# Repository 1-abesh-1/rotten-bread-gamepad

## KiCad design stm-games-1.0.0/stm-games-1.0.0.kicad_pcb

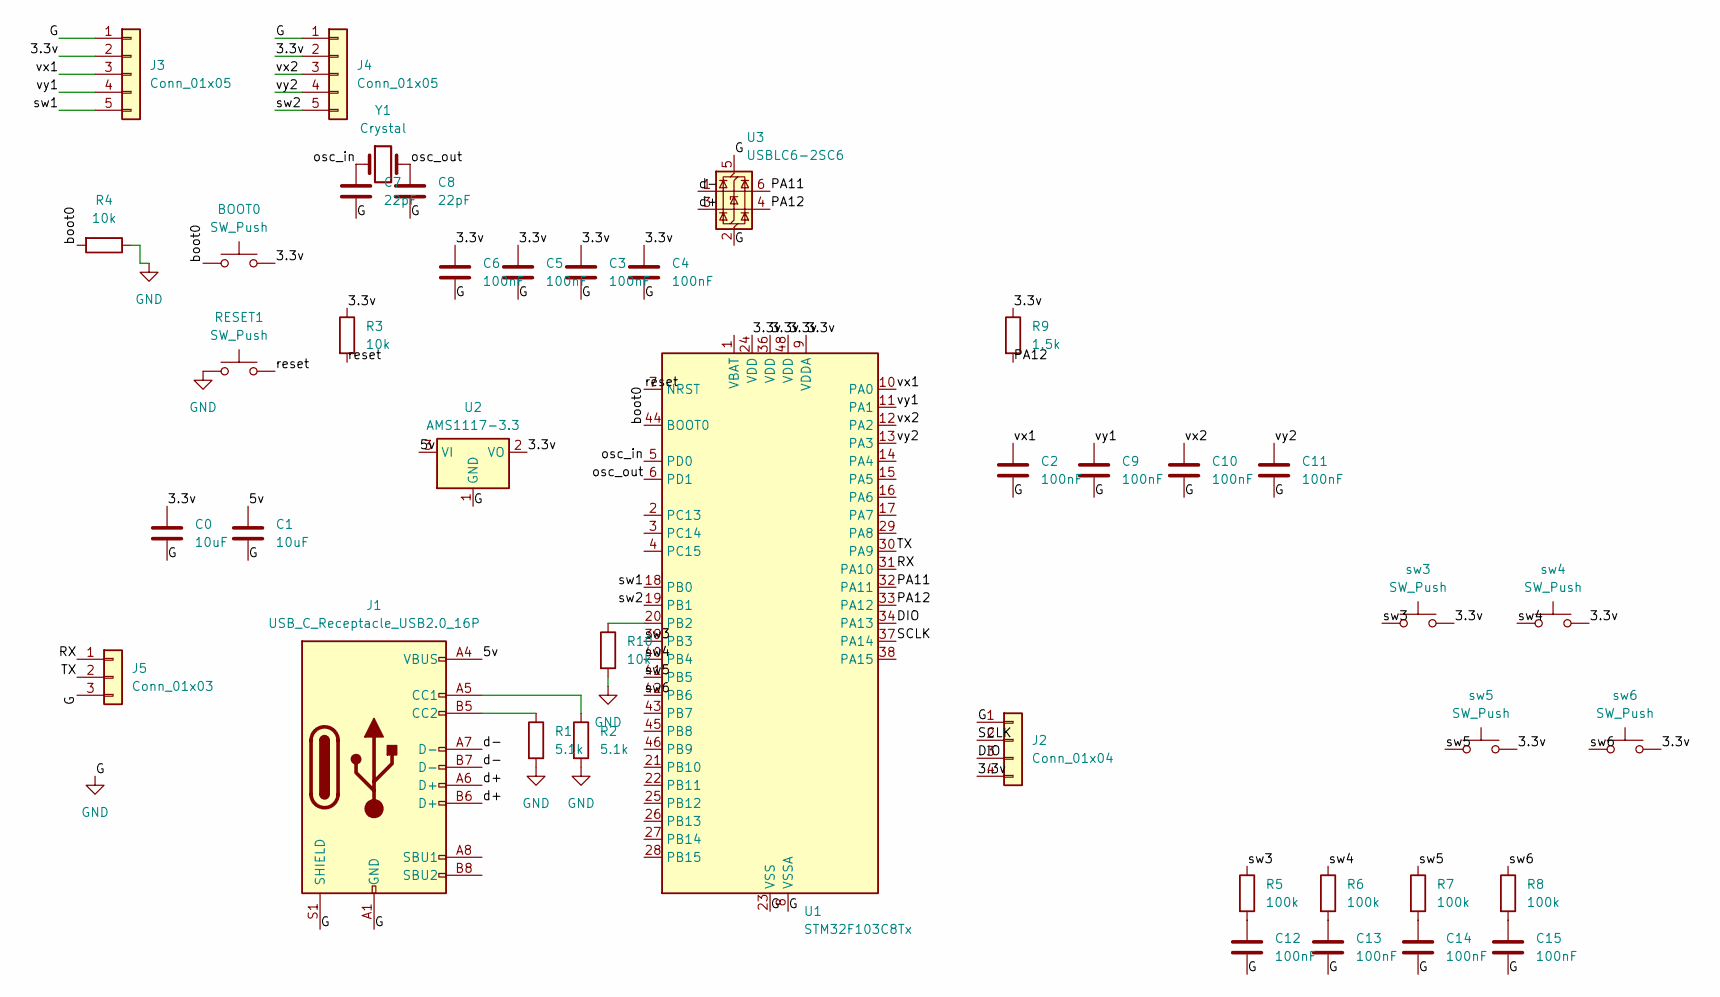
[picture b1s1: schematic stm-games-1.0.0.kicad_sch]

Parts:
BOOT0: SW_Push; SW_PUSH_6mm
C0, C1: 10uF; C_0805_2012Metric
C2, C3, C4, C5, C6, C9, C10, C11, C12, C13, C14, C15: 100nF; C_0805_2012Metric
C7, C8: 22pF; C_0805_2012Metric
J1: USB_C_Receptacle_USB2.0_16P; USB_C_Receptacle_GCT_USB4105-xx-A_16P_TopMnt_Horizontal
J2: Conn_01x04; PinHeader_1x04_P2.54mm_Vertical
J3, J4: Conn_01x05; PinHeader_1x05_P2.54mm_Vertical
J5: Conn_01x03; PinHeader_1x03_P2.54mm_Vertical
R1, R2: 5.1k; R_0805_2012Metric
R3, R4, R10: 10k; R_0805_2012Metric
R5, R6, R7, R8: 100k; R_0805_2012Metric
R9: 1.5k; R_0805_2012Metric
RESET1: SW_Push; SW_PUSH_6mm
U1: STM32F103C8Tx; LQFP-48_7x7mm_P0.5mm
U2: AMS1117-3.3; SOT-223-3_TabPin2
U3: USBLC6-2SC6; SOT-23-6
Y1: Crystal; Crystal_HC49-U_Vertical
sw3, sw4, sw5, sw6: SW_Push; SW_PUSH_6mm

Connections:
/3.3v: BOOT0.2, C0.1, C3.1, C4.1, C5.1, C6.1, J2.4, J3.2, J4.2, R3.1, R9.1, U1.9 (VDDA), U1.24 (VDD), U1.36 (VDD), U1.48 (VDD), U2.2 (VO), sw3.2, sw4.2, sw5.2, sw6.2
/5v: C1.1, J1.A4 (VBUS), J1.A9 (VBUS), J1.B4 (VBUS), J1.B9 (VBUS), U2.3 (VI)
/DIO: J2.3, U1.34 (PA13)
/PA11: U1.32 (PA11), U3.6 (I/O1)
/PA12: R9.2, U1.33 (PA12), U3.4 (I/O2)
/RX: J5.1, U1.31 (PA10)
/SCLK: J2.2, U1.37 (PA14)
/TX: J5.2, U1.30 (PA9)
/boot0: BOOT0.1, R4.2, U1.44 (BOOT0)
/d+: J1.A6 (D+), J1.B6 (D+), U3.3 (I/O2)
/d-: J1.A7 (D-), J1.B7 (D-), U3.1 (I/O1)
/osc_in: C7.1, U1.5 (PD0), Y1.1
/osc_out: C8.1, U1.6 (PD1), Y1.2
/reset: R3.2, RESET1.2, U1.7 (NRST)
/sw1: J3.5, U1.18 (PB0)
/sw2: J4.5, U1.19 (PB1)
/sw3: R5.1, U1.39 (PB3), sw3.1
/sw4: R6.1, U1.40 (PB4), sw4.1
/sw5: R7.1, U1.41 (PB5), sw5.1
/sw6: R8.1, U1.42 (PB6), sw6.1
/vx1: C2.1, J3.3, U1.10 (PA0)
/vx2: C10.1, J4.3, U1.12 (PA2)
/vy1: C9.1, J3.4, U1.11 (PA1)
/vy2: C11.1, J4.4, U1.13 (PA3)
GND: C0.2, C1.2, C2.2, C3.2, C4.2, C5.2, C6.2, C7.2, C8.2, C9.2, C10.2, C11.2, C12.2, C13.2, C14.2, C15.2, J1.A1 (GND), J1.A12 (GND), J1.B1 (GND), J1.B12 (GND), J1.S1 (SHIELD), J2.1, J3.1, J4.1, J5.3, R1.2, R2.2, R4.1, R10.2, RESET1.1, U1.8 (VSSA), U1.23 (VSS), U1.35 (VSS), U1.47 (VSS), U2.1 (GND), U3.2 (GND), U3.5 (VBUS)
unnamed: C12.1, R5.2
unnamed: C13.1, R6.2
unnamed: C14.1, R7.2
unnamed: C15.1, R8.2
unnamed: J1.A5 (CC1), R2.1
unnamed: J1.B5 (CC2), R1.1
unnamed: R10.1, U1.20 (PB2)

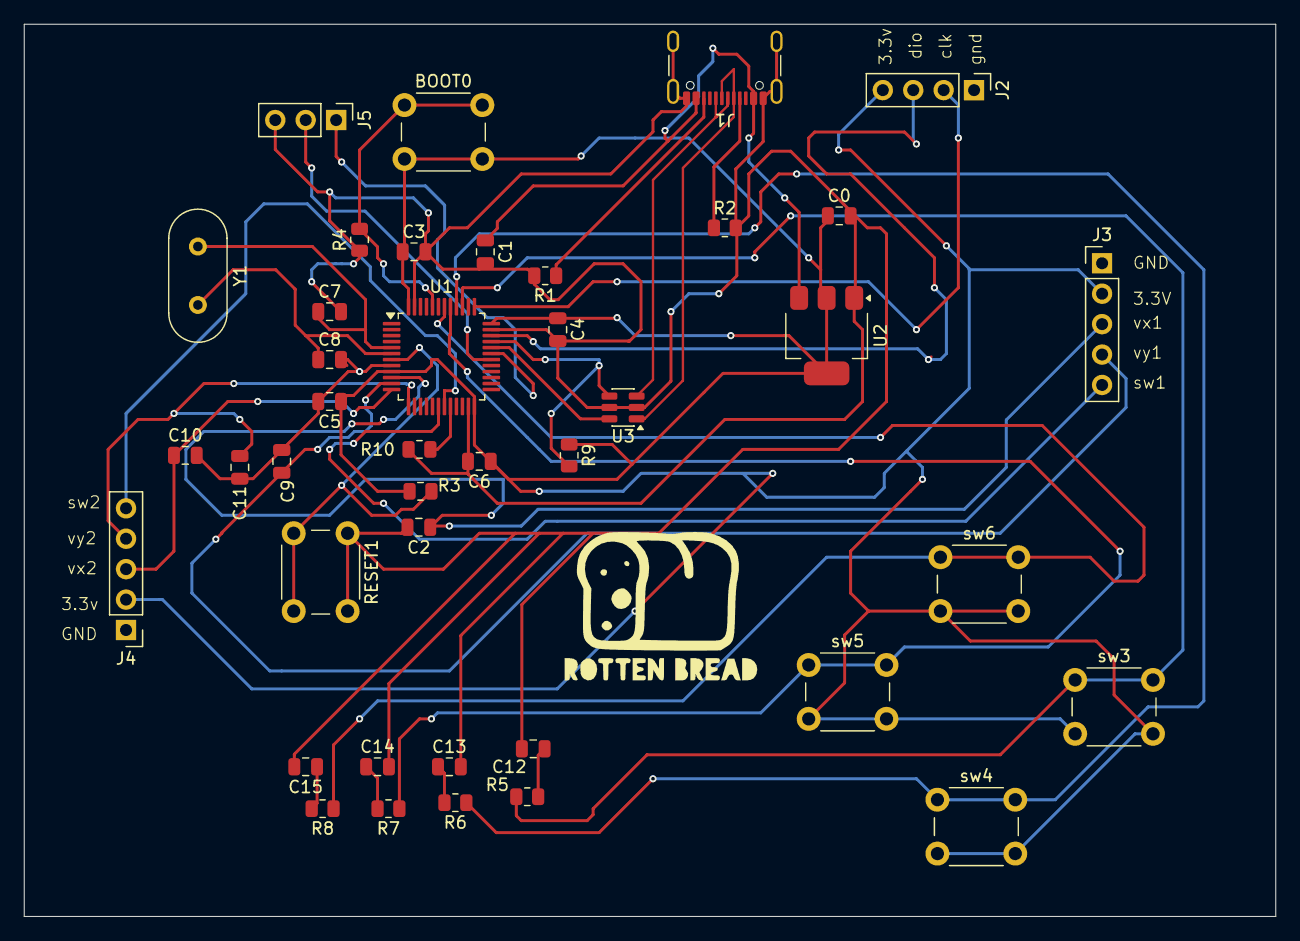
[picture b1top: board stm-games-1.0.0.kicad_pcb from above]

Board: 2 copper layers, 104.5 x 74.5 mm, 41 parts (0 on the bottom side), 32 nets.
